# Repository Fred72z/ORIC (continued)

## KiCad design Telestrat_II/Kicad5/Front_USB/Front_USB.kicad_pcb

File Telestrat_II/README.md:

# TELESTRAT II

Le TELESTRAT II est un TELESTRAT au format mini-ITX qui prend place dans un boîtier HTPC.
En plus des caractéristiques du TELESTRAT, la machine dispose en interne d'une horloge RTC, de 512Ko de ROM et de 144Ko de RAM et d'un lecteur GOTEK.
La machine est un mix entre l'ORIC ATMOS et le TELESTRAT. Elle dispose de 8 modes de fonctionnement allant de l'ORIC1 au TELESTRAT.
Elle est parfaitement compatible avec ses prédécesseurs ORIC1/ATMOS et microdisc.

Mode ORIC1

Mode ORIC ATMOS avec SEDORIC

Mode TELESTRAT HYPERBASIC

Intérieur de la boîte

Platine principale seule

# Connecteurs

Les connecteurs sont tous disposés à l'arrière de la machine à l'exception du port d'extension placé sur la carte mère.

**AUDIO/VIDEO**

- 1 : REMOTE 
- 2 : +5V
- 3 : REMOTE 
- 4 : K7 IN
- 5 : K7 OUT
- 6 : NC
- 7 : SYNC
- 8 : ROUGE
- 9 : SOUND OUT
- 10 : GND
- 11 : VERT
- 12 : BLEU
- 13 : GND
- SHIELD : GND

**MINITEL/MIDI**

- 1  : GND
- 2  : BAUD_RATE
- 3  : PA3
- 4  : MINITEL_DATA_OUT
- 5  : PA6
- 6  : MINITEL_DATA_IN
- 7  : CB2
- 8  : CARRIER
- 9  : NC
- 10 : NC
- 11 : CA1
- 12 : CB1
- 13 : +5V
- 14 : GND

**IMPRIMANTE**

- 1  : /STB
- 3  : D0
- 5  : D1
 -7  : D2
 -9  : D3
- 11 : D4
- 13 : D5
- 15 : D6
- 17 : D7
- 19 : /ACK
- 2,4,...,20 : GND

**CLAVIER**

- 1  : COL0
- 2  : COL1
- 3  : COL2
- 4  : COL3
- 5  : COL7
- 6  : KBD2
- 7  : KBD1
- 8  : KBD0
- 9  : COL6
- 10 : COL5
- 11 : COL4
- 12 : KB
- 13 : +5V
- SHIELD : GND

**JOYSTICK GAUCHE**

- 1 : HAUT
- 2 : BAS
- 3 : GAUCHE
- 4 : DROIT
- 5 : NC
- 6 : TIR
- 7 : +5V
- 8 : GND
- 9 : NC

**JOYSTICK DROIT**

- 1 : HAUT
- 2 : BAS
- 3 : GAUCHE
- 4 : DROIT
- 5 : TIR2
- 6 : TIR
- 7 : +5V
- 8 : GND
- 9 : TIR3

**EXPANSION**
Un port d'extension est placé sur la carte principale. Il permet d'ajouter des périphériques en page 3 uniquement. Son brochage est le suivant:
[à venir]

# Modes de fonctionnement

Le Telestrat II dispose de 8 modes différents permettant de reproduire le fonctionnement de l'ORIC1, l'oric ATMOS ou l'oric TELESTRAT. Ces modes sont sélectionnés grace à 3 micro-interrupteurs "piano" accessibles à l'arrière de la machine.

4 modes sont réservés aux ORIC1/ATMOS et 4 modes sont réservés au TELESTRAT.

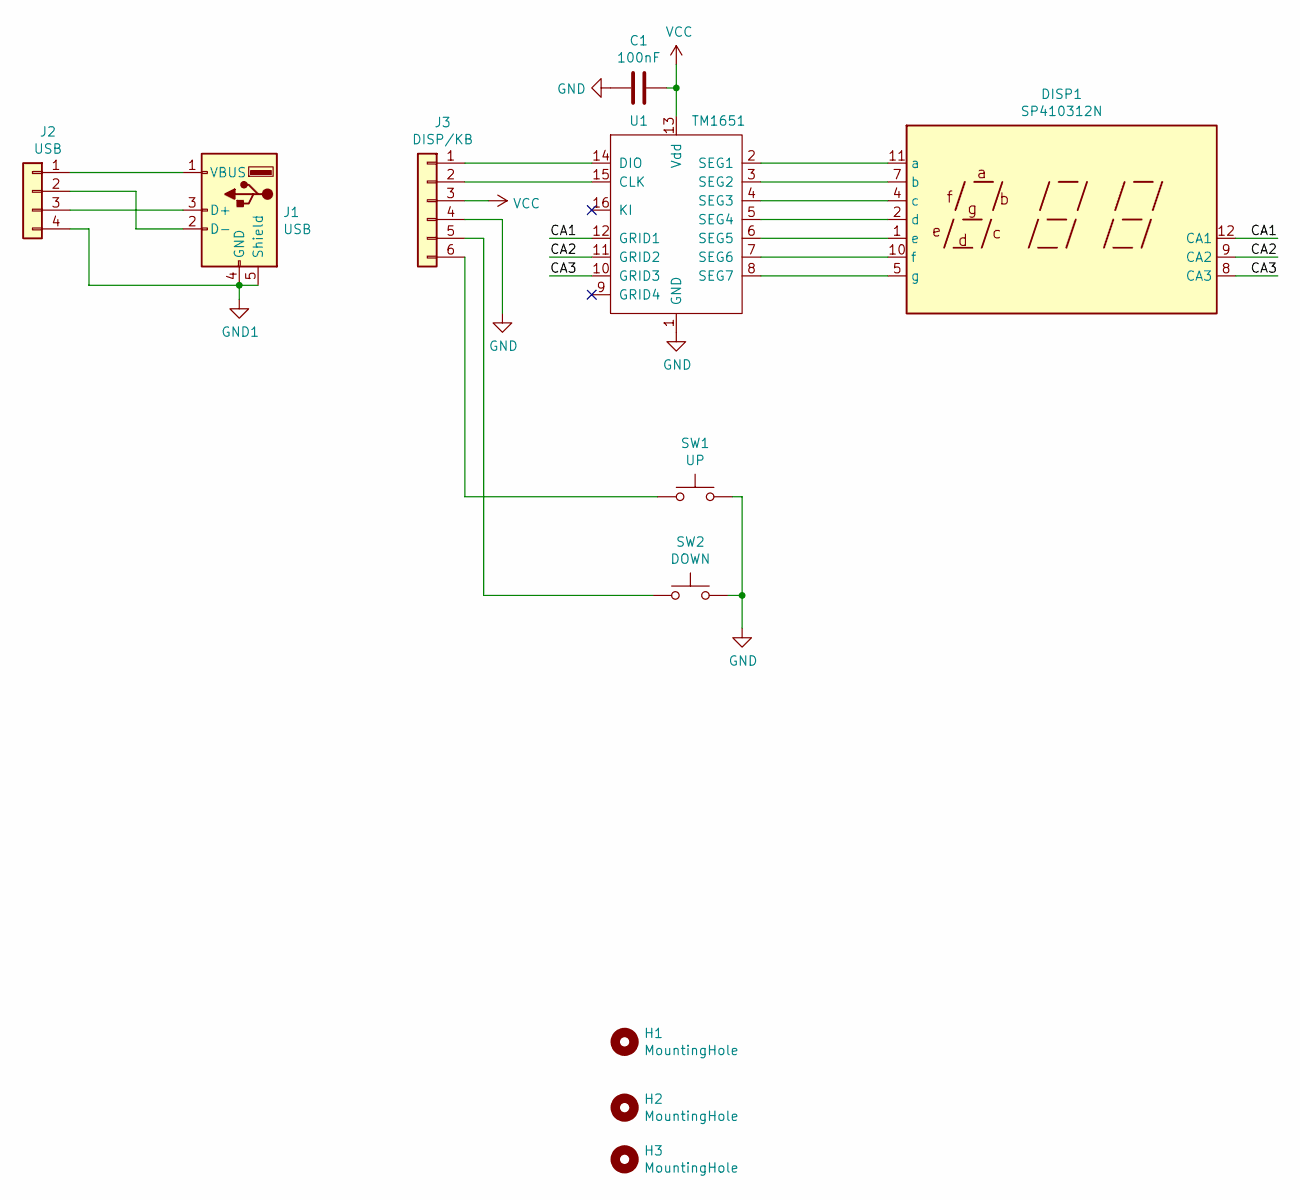
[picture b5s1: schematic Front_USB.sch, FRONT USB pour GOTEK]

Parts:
C1: 100nF; C_0805_2012Metric
DISP1: SP410312N; SP410312SPN
H1, H2: MountingHole; MountingHole_4.3mm_M4
H3: MountingHole; MountingHole_2.2mm_M2
J1: USB; USB_A_Vertical
J2: USB; PinHeader_1x04_P2.54mm_Vertical
J3: DISP/KB; PinHeader_1x06_P2.54mm_Vertical
SW1: UP; SW_PUSH_6mm
SW2: DOWN; SW_PUSH_6mm
U1: TM1651; SO-16_3.9x9.9mm_P1.27mm

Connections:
/CA1: DISP1.12 (CA1), U1.12 (GRID1)
/CA2: DISP1.9 (CA2), U1.11 (GRID2)
/CA3: DISP1.8 (CA3), U1.10 (GRID3)
GND: C1.2, J3.4, SW1.2, SW2.2, U1.1 (GND)
GND1: J1.4 (GND), J1.5 (Shield), J2.4
unnamed: DISP1.1 (e), U1.6 (SEG5)
unnamed: DISP1.2 (d), U1.5 (SEG4)
unnamed: DISP1.4 (c), U1.4 (SEG3)
unnamed: DISP1.5 (g), U1.8 (SEG7)
unnamed: DISP1.7 (b), U1.3 (SEG2)
unnamed: DISP1.10 (f), U1.7 (SEG6)
unnamed: DISP1.11 (a), U1.2 (SEG1)
unnamed: J1.1 (VBUS), J2.1
unnamed: J1.2 (D-), J2.2
unnamed: J1.3 (D+), J2.3
unnamed: J3.1, U1.14 (DIO)
unnamed: J3.2, U1.15 (CLK)
unnamed: J3.5, SW2.1
unnamed: J3.6, SW1.1
VCC: C1.1, J3.3, U1.13 (Vdd)

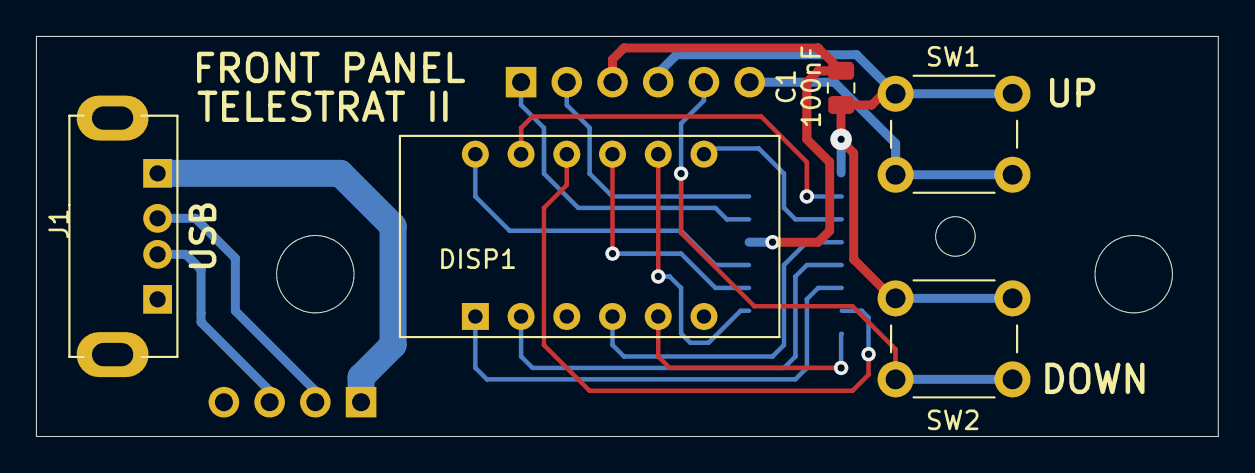
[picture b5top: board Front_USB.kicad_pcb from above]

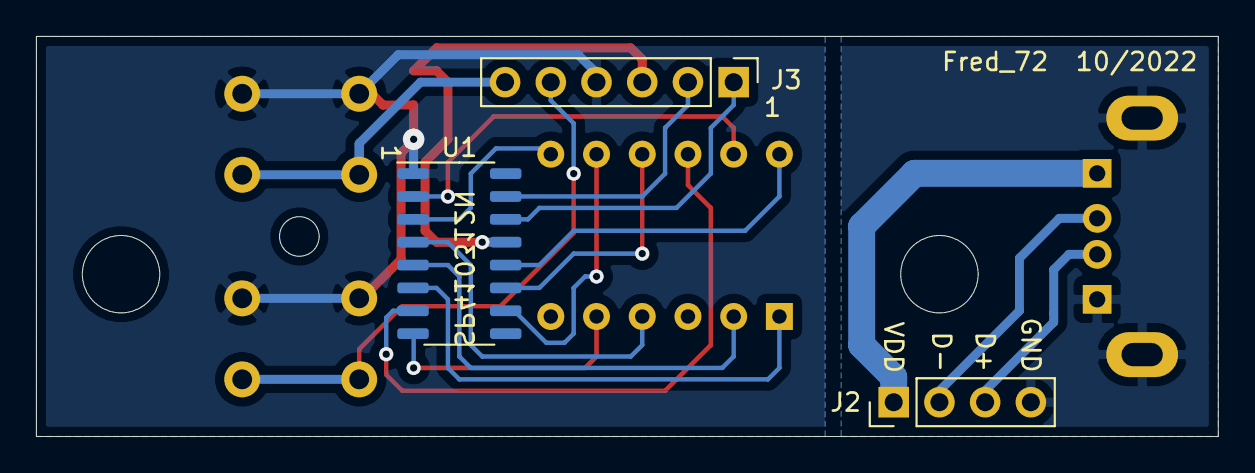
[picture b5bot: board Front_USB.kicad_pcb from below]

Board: 2 copper layers, 65.7 x 22.2 mm, 11 parts (3 on the bottom side), 20 nets.

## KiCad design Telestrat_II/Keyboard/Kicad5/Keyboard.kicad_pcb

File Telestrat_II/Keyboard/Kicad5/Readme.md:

# CLAVIER TELESTRAT II

Les touches du clavier sont des CHERRY ou GATERON (rouge).
La barre d'espace reçoit 2 touches (préférable) ou une seule touche (ajout d'une barre pour l'équilibrer).
La vue 3D du PCB montre 3 touches pour la barre d'espace mais il ne faut en mettre qu'une ou deux.

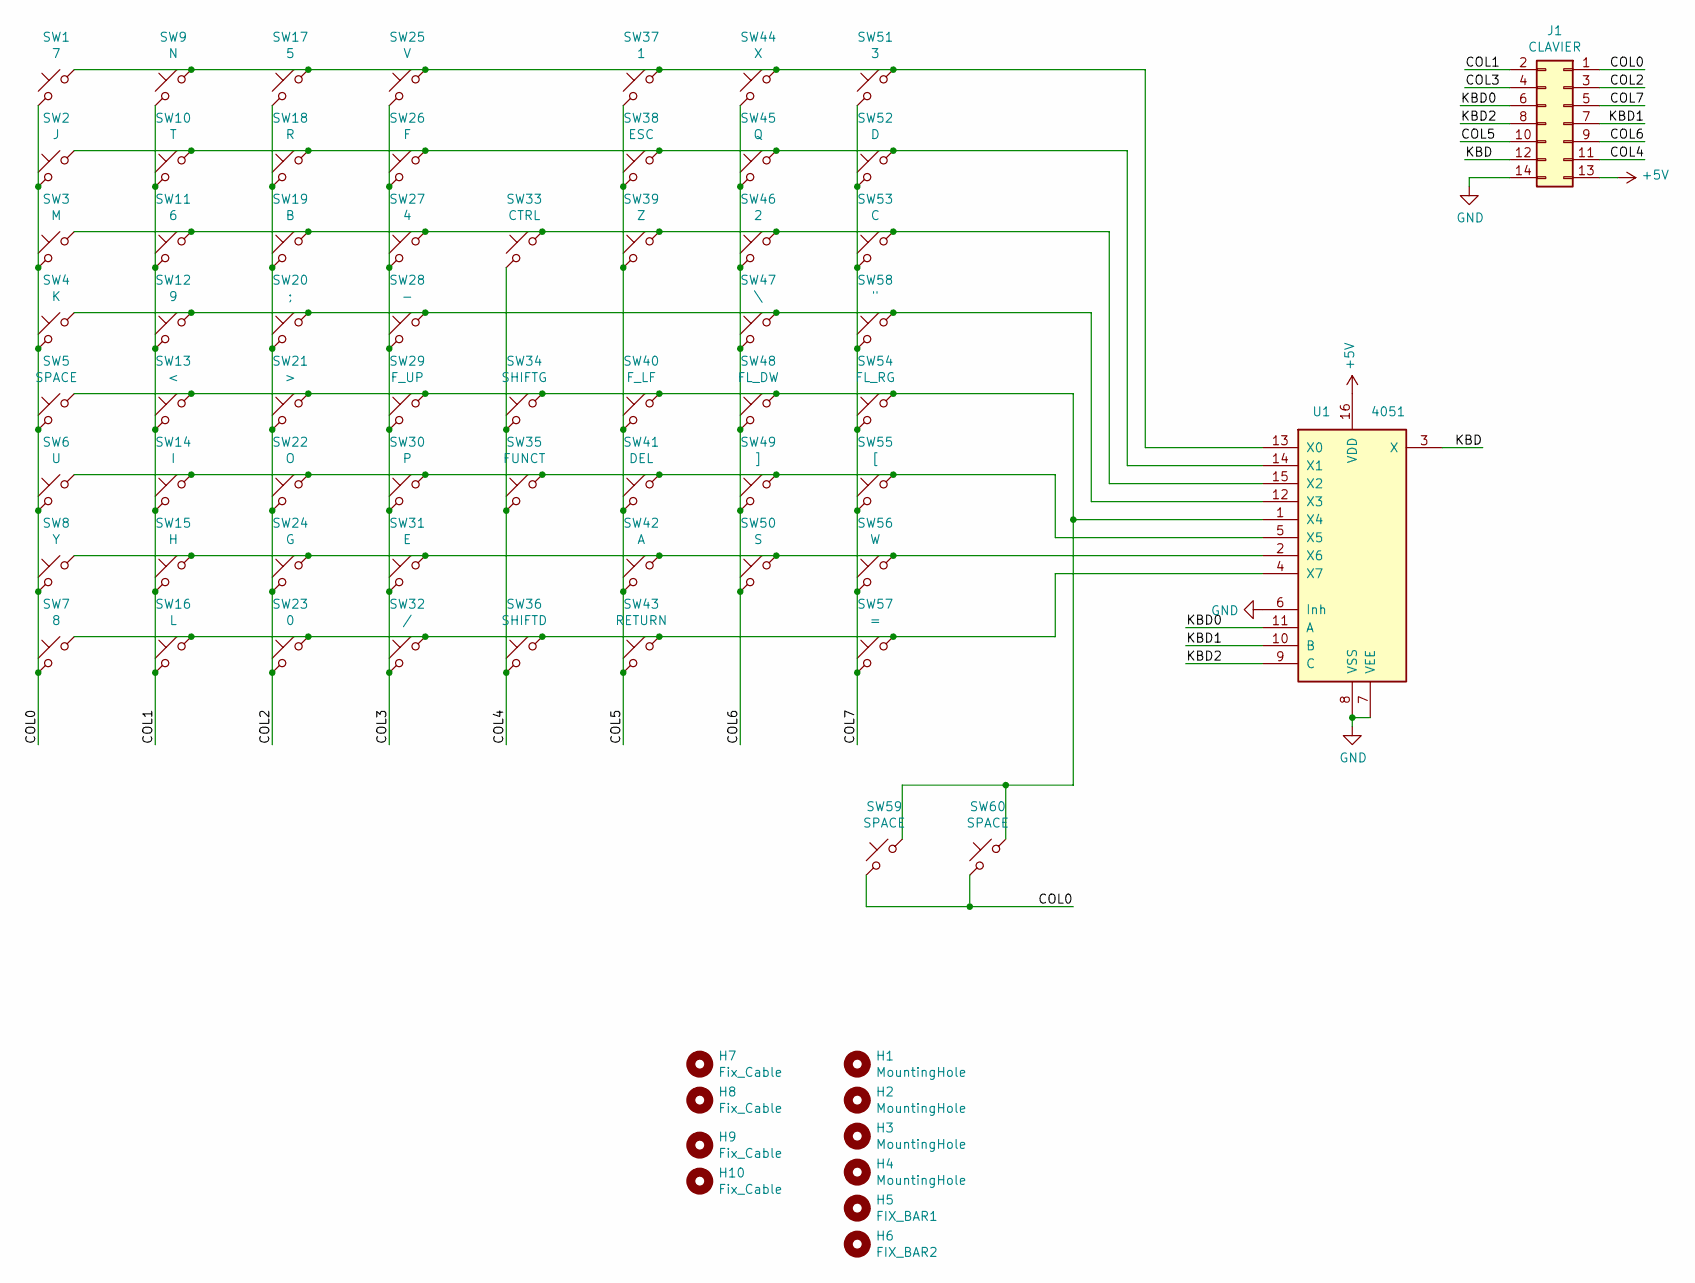
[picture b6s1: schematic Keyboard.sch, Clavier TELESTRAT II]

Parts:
H1, H2, H3, H4: MountingHole; MountingHole_3.2mm_M3_DIN965_Pad
H5: FIX_BAR1; MountingHole_3.2mm_M3_DIN965_Pad
H6: FIX_BAR2; MountingHole_3.2mm_M3_DIN965_Pad
H7, H8, H9, H10: Fix_Cable; MountingHole_2.2mm_M2_DIN965_Pad
J1: CLAVIER; PinHeader_2x07_P2.54mm_Vertical
SW1: 7; SW_Gateron_MX_1.00u_Plate
SW2: J; SW_Gateron_MX_1.00u_Plate
SW3: M; SW_Gateron_MX_1.00u_Plate
SW4: K; SW_Gateron_MX_1.00u_Plate
SW5: SPACE; SW_Gateron_MX_6.25u_Plate
SW6: U; SW_Gateron_MX_1.00u_Plate
SW7: 8; SW_Gateron_MX_1.00u_Plate
SW8: Y; SW_Gateron_MX_1.00u_Plate
SW9: N; SW_Gateron_MX_1.00u_Plate
SW10: T; SW_Gateron_MX_1.00u_Plate
SW11: 6; SW_Gateron_MX_1.00u_Plate
SW12: 9; SW_Gateron_MX_1.00u_Plate
SW13: <; SW_Gateron_MX_1.00u_Plate
SW14: I; SW_Gateron_MX_1.00u_Plate
SW15: H; SW_Gateron_MX_1.00u_Plate
SW16: L; SW_Gateron_MX_1.00u_Plate
SW17: 5; SW_Gateron_MX_1.00u_Plate
SW18: R; SW_Gateron_MX_1.00u_Plate
SW19: B; SW_Gateron_MX_1.00u_Plate
SW20: ;; SW_Gateron_MX_1.00u_Plate
SW21: >; SW_Gateron_MX_1.00u_Plate
SW22: O; SW_Gateron_MX_1.00u_Plate
SW23: 0; SW_Gateron_MX_1.00u_Plate
SW24: G; SW_Gateron_MX_1.00u_Plate
SW25: V; SW_Gateron_MX_1.00u_Plate
SW26: F; SW_Gateron_MX_1.00u_Plate
SW27: 4; SW_Gateron_MX_1.00u_Plate
SW28: -; SW_Gateron_MX_1.00u_Plate
SW29: F_UP; SW_Gateron_MX_1.00u_Plate
SW30: P; SW_Gateron_MX_1.00u_Plate
SW31: E; SW_Gateron_MX_1.00u_Plate
SW32: /; SW_Gateron_MX_1.00u_Plate
SW33: CTRL; SW_Gateron_MX_1.25u_Plate
SW34: SHIFTG; SW_Gateron_MX_1.25u_Plate
SW35: FUNCT; SW_Gateron_MX_1.25u_Plate
SW36: SHIFTD; SW_Gateron_MX_2.25u_Plate
SW37: 1; SW_Gateron_MX_1.00u_Plate
SW38: ESC; SW_Gateron_MX_1.00u_Plate
SW39: Z; SW_Gateron_MX_1.00u_Plate
SW40: F_LF; SW_Gateron_MX_1.00u_Plate
SW41: DEL; SW_Gateron_MX_2.00u_Plate
SW42: A; SW_Gateron_MX_1.00u_Plate
SW43: RETURN; SW_Gateron_MX_2.25u_Plate
SW44: X; SW_Gateron_MX_1.00u_Plate
SW45: Q; SW_Gateron_MX_1.00u_Plate
SW46: 2; SW_Gateron_MX_1.00u_Plate
SW47: \\; SW_Gateron_MX_1.50u_Plate
SW48: FL_DW; SW_Gateron_MX_1.00u_Plate
SW49: ]; SW_Gateron_MX_1.00u_Plate
SW50: S; SW_Gateron_MX_1.00u_Plate
SW51: 3; SW_Gateron_MX_1.00u_Plate
SW52: D; SW_Gateron_MX_1.00u_Plate
SW53: C; SW_Gateron_MX_1.00u_Plate
SW54: FL_RG; SW_Gateron_MX_1.00u_Plate
SW55: [; SW_Gateron_MX_1.00u_Plate
SW56: W; SW_Gateron_MX_1.00u_Plate
SW57: =; SW_Gateron_MX_1.00u_Plate
SW58: \"; SW_Gateron_MX_1.00u_Plate
SW59, SW60: SPACE; SW_Gateron_MX_1.00u_Plate
U1: 4051; DIP-16_W7.62mm

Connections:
+5V: J1.13, U1.16 (VDD)
/COL0: J1.1, SW1.2, SW2.2, SW3.2, SW4.2, SW5.2, SW6.2, SW7.2, SW8.2, SW59.2, SW60.2
/COL1: J1.2, SW9.2, SW10.2, SW11.2, SW12.2, SW13.2, SW14.2, SW15.2, SW16.2
/COL2: J1.3, SW17.2, SW18.2, SW19.2, SW20.2, SW21.2, SW22.2, SW23.2, SW24.2
/COL3: J1.4, SW25.2, SW26.2, SW27.2, SW28.2, SW29.2, SW30.2, SW31.2, SW32.2
/COL4: J1.11, SW33.2, SW34.2, SW35.2, SW36.2
/COL5: J1.10, SW37.2, SW38.2, SW39.2, SW40.2, SW41.2, SW42.2, SW43.2
/COL6: J1.9, SW44.2, SW45.2, SW46.2, SW47.2, SW48.2, SW49.2, SW50.2
/COL7: J1.5, SW51.2, SW52.2, SW53.2, SW54.2, SW55.2, SW56.2, SW57.2, SW58.2
/KBD: J1.12, U1.3 (X)
/KBD0: J1.6, U1.11 (A)
/KBD1: J1.7, U1.10 (B)
/KBD2: J1.8, U1.9 (C)
GND: J1.14, U1.6 (Inh), U1.7 (VEE), U1.8 (VSS)
unnamed: SW1.1, SW9.1, SW17.1, SW25.1, SW37.1, SW44.1, SW51.1, U1.13 (X0)
unnamed: SW2.1, SW10.1, SW18.1, SW26.1, SW38.1, SW45.1, SW52.1, U1.14 (X1)
unnamed: SW3.1, SW11.1, SW19.1, SW27.1, SW33.1, SW39.1, SW46.1, SW53.1, U1.15 (X2)
unnamed: SW4.1, SW12.1, SW20.1, SW28.1, SW47.1, SW58.1, U1.12 (X3)
unnamed: SW5.1, SW13.1, SW21.1, SW29.1, SW34.1, SW40.1, SW48.1, SW54.1, SW59.1, SW60.1, U1.1 (X4)
unnamed: SW6.1, SW14.1, SW22.1, SW30.1, SW35.1, SW41.1, SW49.1, SW55.1, U1.5 (X5)
unnamed: SW8.1, SW15.1, SW24.1, SW31.1, SW42.1, SW50.1, SW56.1, U1.2 (X6)
unnamed: SW7.1, SW16.1, SW23.1, SW32.1, SW36.1, SW43.1, SW57.1, U1.4 (X7)

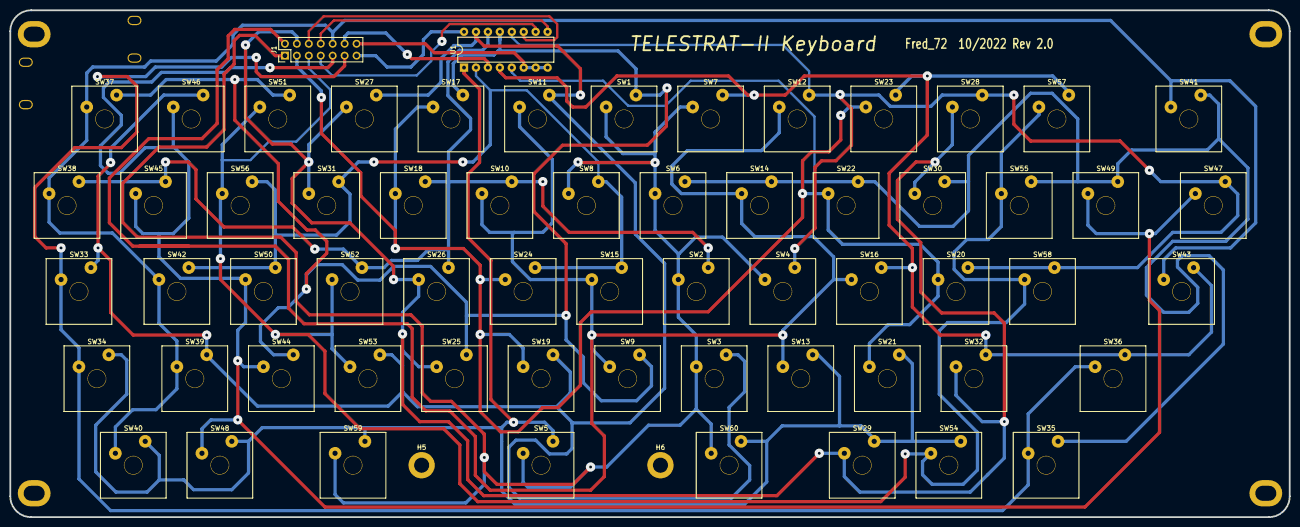
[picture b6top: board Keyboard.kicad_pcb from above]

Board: 2 copper layers, 272.2 x 107.8 mm, 72 parts (0 on the bottom side), 22 nets.

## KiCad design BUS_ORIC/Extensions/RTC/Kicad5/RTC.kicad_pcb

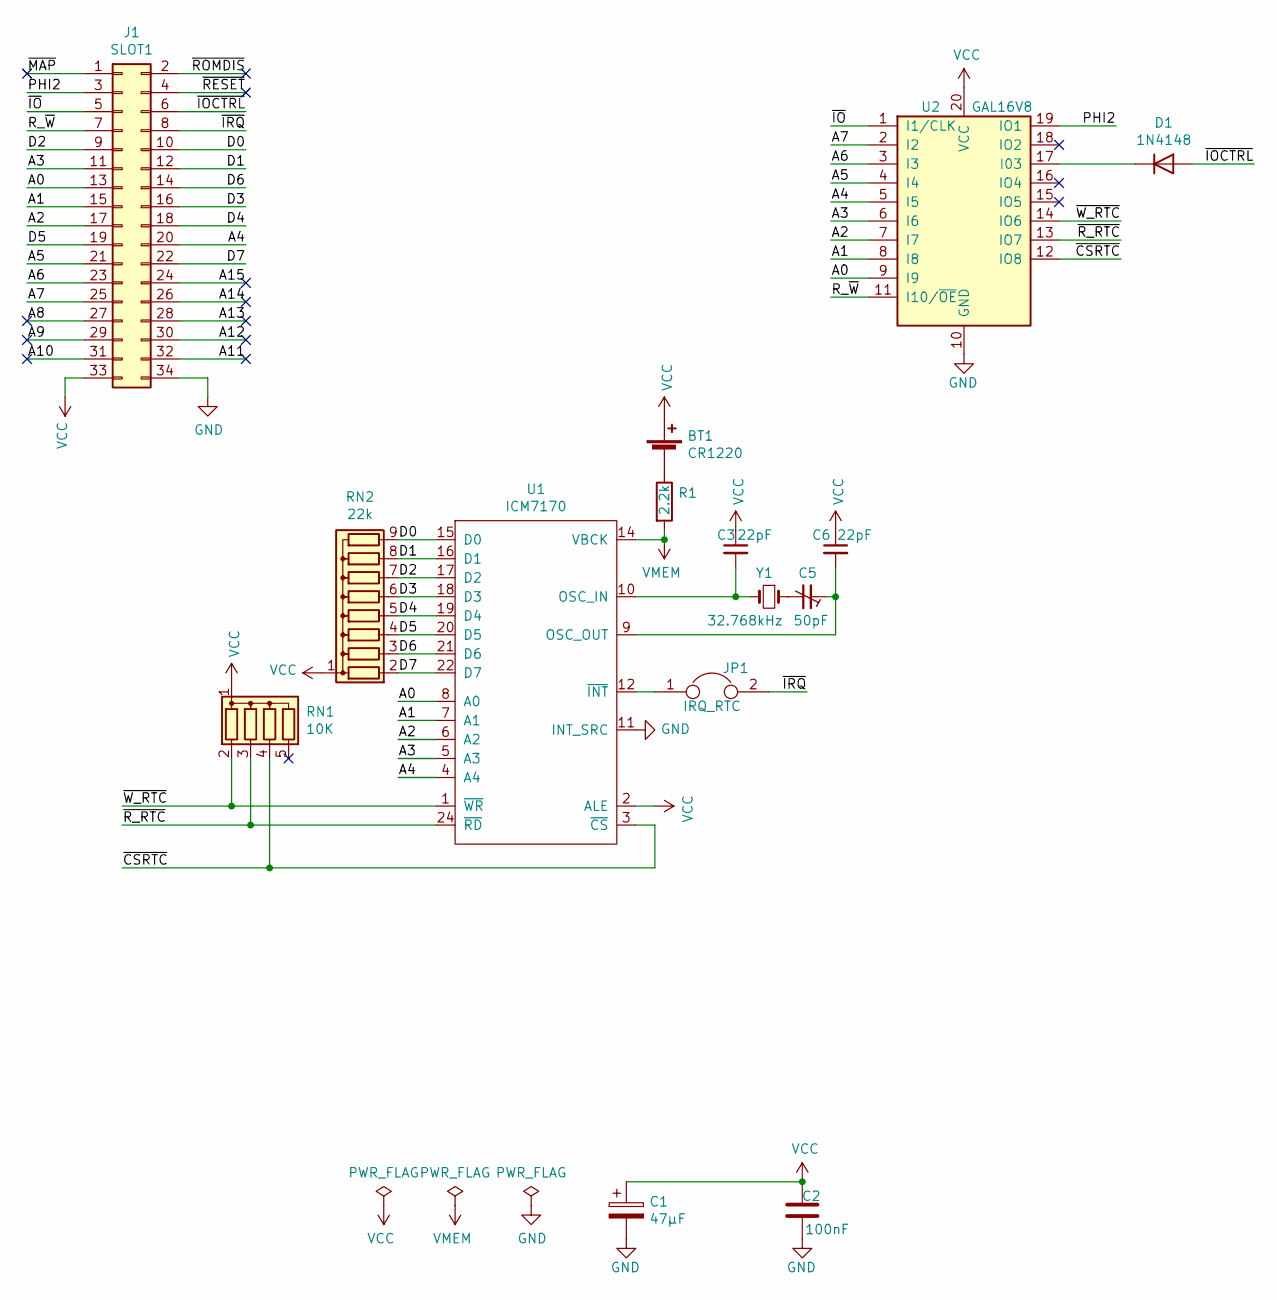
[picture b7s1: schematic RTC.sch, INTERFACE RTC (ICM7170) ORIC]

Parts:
BT1: CR1220; BatteryHolder_BC501SM
C1: 47µF; CP_Radial_D5.0mm_P2.00mm
C2: 100nF; C_Rect_L7.0mm_W2.5mm_P5.00mm
C3, C6: 22pF; C_Disc_D4.3mm_W1.9mm_P5.00mm
C5: 50pF; Trimmer_Cap_TZ03F
D1: 1N4148; D_DO-35_SOD27_P7.62mm_Horizontal
J1: SLOT1; IDC-Header_2x17_P2.54mm_Horizontal
JP1: IRQ_RTC; PinHeader_1x02_P2.54mm_Vertical
R1: 2.2k; R_Axial_DIN0204_L3.6mm_D1.6mm_P7.62mm_Horizontal
RN1: 10K; R_Array_SIP5
RN2: 22k; R_Array_SIP9
U1: ICM7170; DIP-24_W15.24mm_LongPads
U2: GAL16V8; DIP-20_W7.62mm_LongPads
Y1: 32.768kHz; Crystal_AT310_D3.0mm_L10.0mm_Horizontal_1EP_style2

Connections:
/A0: J1.13, U1.8 (A0), U2.9 (I9)
/A1: J1.15, U1.7 (A1), U2.8 (I8)
/A2: J1.17, U1.6 (A2), U2.7 (I7)
/A3: J1.11, U1.5 (A3), U2.6 (I6)
/A4: J1.20, U1.4 (A4), U2.5 (I5)
/A5: J1.21, U2.4 (I4)
/A6: J1.23, U2.3 (I3)
/A7: J1.25, U2.2 (I2)
/A8: J1.27
/A9: J1.29
/A10: J1.31
/A11: J1.32
/A12: J1.30
/A13: J1.28
/A14: J1.26
/A15: J1.24
/D0: J1.10, RN2.9 (R8), U1.15 (D0)
/D1: J1.12, RN2.8 (R7), U1.16 (D1)
/D2: J1.9, RN2.7 (R6), U1.17 (D2)
/D3: J1.16, RN2.6 (R5), U1.18 (D3)
/D4: J1.18, RN2.5 (R4), U1.19 (D4)
/D5: J1.19, RN2.4 (R3), U1.20 (D5)
/D6: J1.14, RN2.3 (R2), U1.21 (D6)
/D7: J1.22, RN2.2 (R1), U1.22 (D7)
/PHI2: J1.3, U2.19 (IO1)
/R_~W: J1.7, U2.11 (I10/~OE~)
/~CSRTC: RN1.4 (R3), U1.3 (~CS), U2.12 (IO8)
/~IO: J1.5, U2.1 (I1/CLK)
/~IOCTRL: D1.2 (A), J1.6
/~IRQ: J1.8, JP1.2
/~MAP: J1.1
/~RESET: J1.4
/~ROMDIS: J1.2
/~R_RTC: RN1.3 (R2), U1.24 (~RD), U2.13 (IO7)
/~W_RTC: RN1.2 (R1), U1.1 (~WR), U2.14 (IO6)
GND: C1.2, C2.1, J1.34, U1.11 (INT_SRC), U1.13 (GND), U2.10 (GND)
unnamed: BT1.2 (-), R1.1
unnamed: C3.2, U1.10 (OSC_IN), Y1.2
unnamed: C5.1, C6.2, U1.9 (OSC_OUT)
unnamed: C5.2, Y1.1
unnamed: D1.1 (K), U2.17 (I03)
unnamed: JP1.1, U1.12 (~INT)
VCC: BT1.1 (+), C1.1, C2.2, C3.1, C6.1, J1.33, RN1.1 (common), RN2.1 (common), U1.2 (ALE), U1.23 (VCC), U2.20 (VCC)
VMEM: R1.2, U1.14 (VBCK)

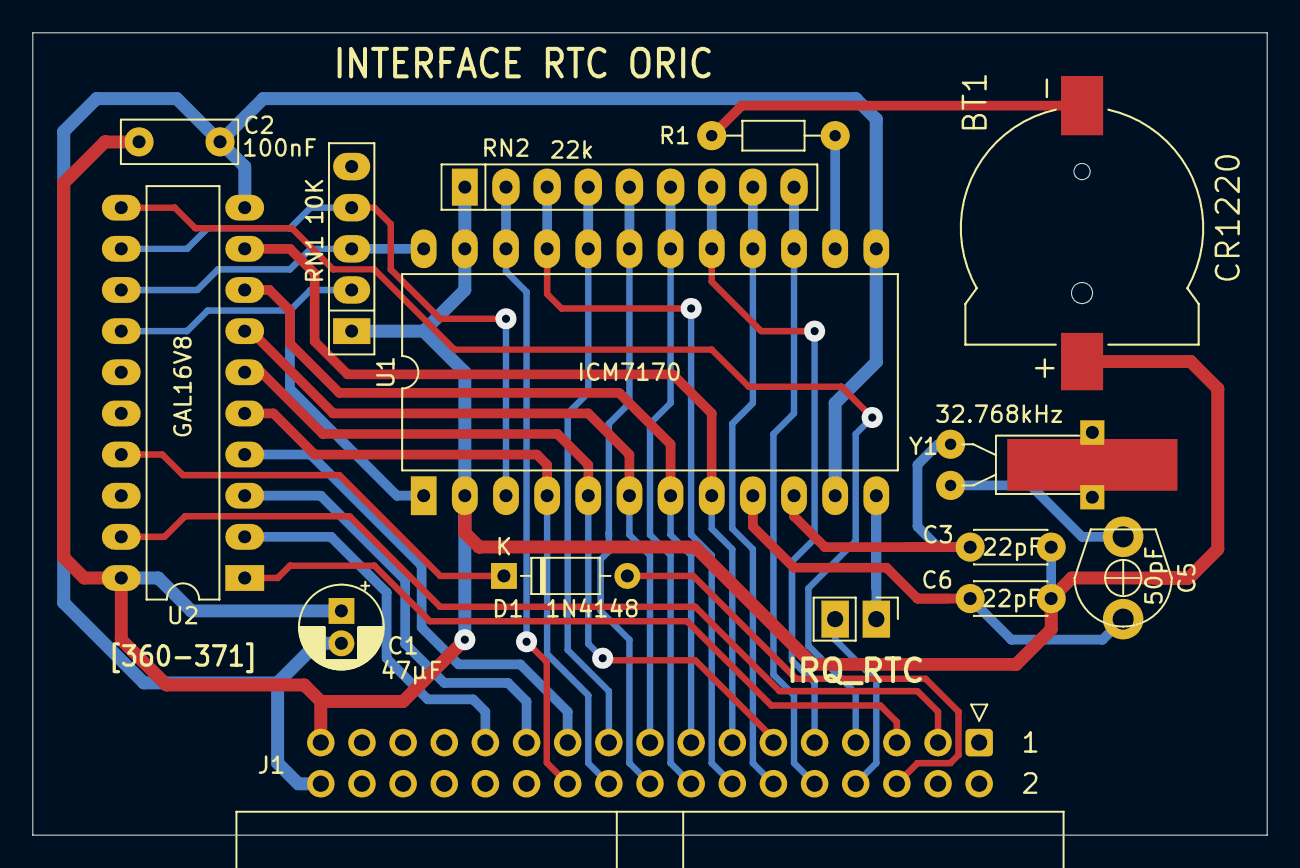
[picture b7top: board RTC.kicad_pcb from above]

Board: 2 copper layers, 76.2 x 49.5 mm, 15 parts (0 on the bottom side), 33 nets.

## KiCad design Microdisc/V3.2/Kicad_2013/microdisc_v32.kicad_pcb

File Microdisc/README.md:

# Microdisc
Nouveau contrôleur compatible microdisc

Ce contrôleur reprend le schéma du contrôleur microdisc original mais remplace les portes logiques par un circuit CPLD afin de réduire sa taille.
Il se loge ainsi sous un lecteur de disquettes 3.5" classique pour la version 3.2 et sous un lecteur gotek pour la version 3.4 (un peu plus court).
Ils sont presque identiques sauf au niveau des buffers 74HCT541 pour la version 3.2 et 74HCT244 pour la version 3.4.

__Version 3.2 (lecteur 3.5")__

__Version 3.4 (lecteur Gotek)__

Le fonctionnement reste identique au microdisc d'origine.

La ROM est identique pour les 2 versions. Le PCB accepte des 27C64/128/256 ou 512.
Mais le fonctionnement est très sensible aux composants utilisés (classique avec l'Oric), notamment l'EPROM et les Buffers.
J'obtiens un bon fonctionnement avec des EPROM 27C512 "petite puce" et des circuits HCT.

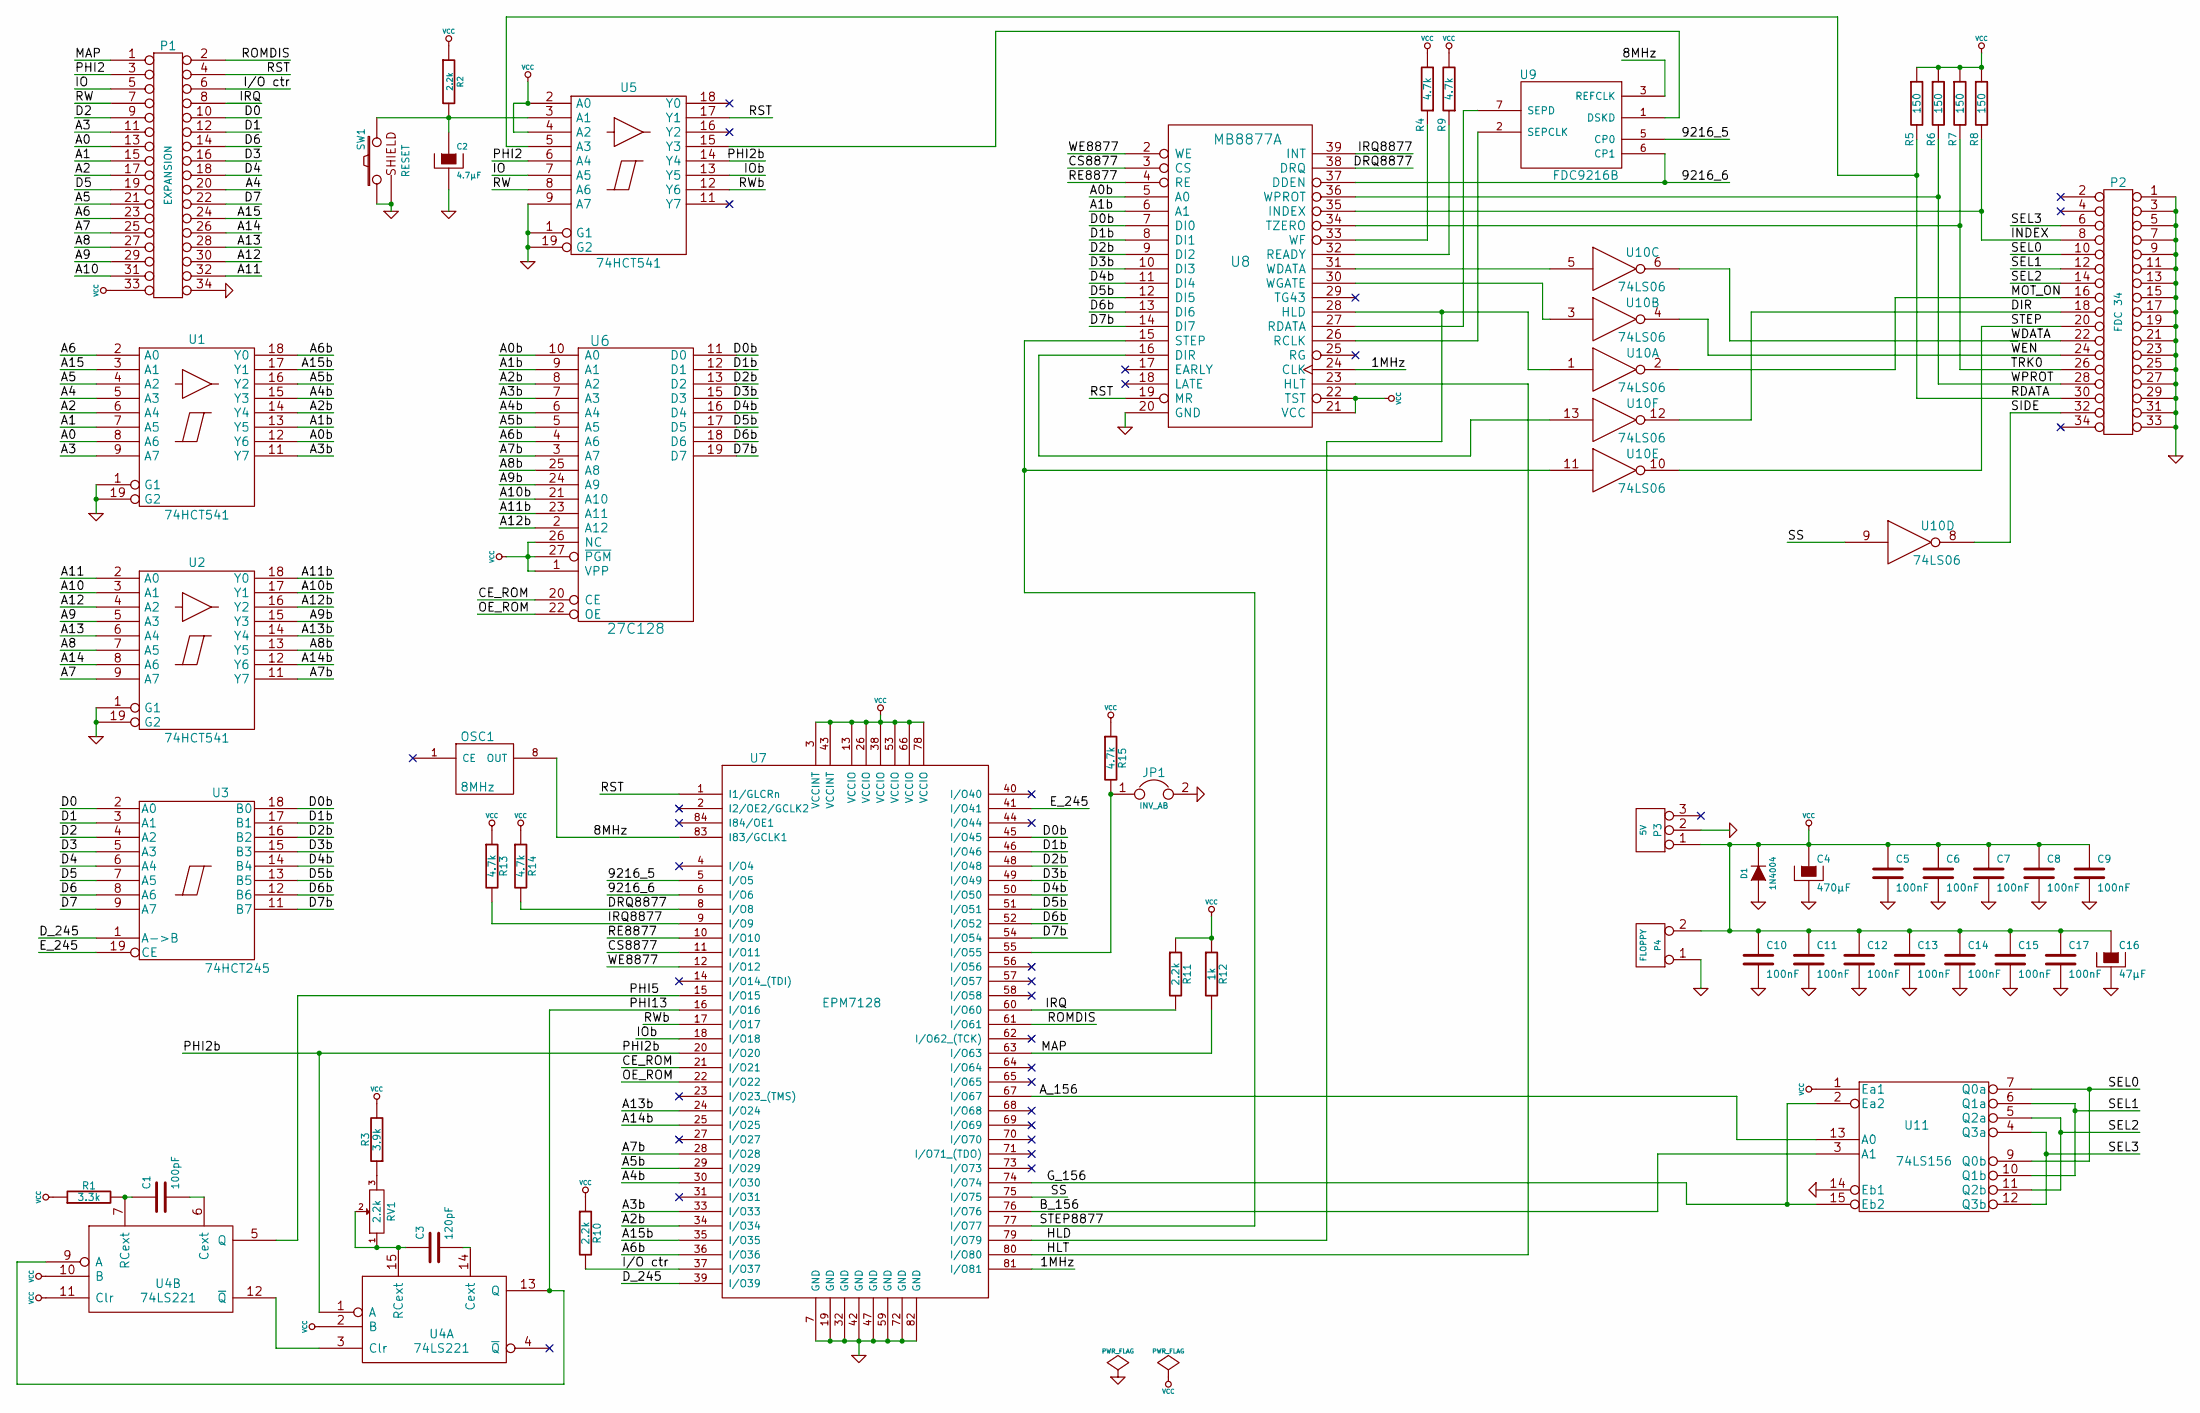
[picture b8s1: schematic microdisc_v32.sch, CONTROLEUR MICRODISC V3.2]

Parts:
C1: 100pF
C2: 4.7µF
C3: 120pF
C4: 470µF
C5, C6, C7, C8, C9, C10, C11, C12, C13, C14, C15, C17: 100nF
C16: 47µF
D1: 1N4004
JP1: INV_AB
OSC1: 8MHz
P1: EXPANSION
P2: FDC 34
P3: 5V
P4: FLOPPY
R1: 3.3k
R2, R10, R11: 2.2k
R3: 3.9k
R4, R9, R13, R14, R15: 4.7k
R5, R6, R7, R8: 150
R12: 1k
RV1: 2.2k
SW1: RESET
U1, U2, U5: 74HCT541
U3: 74HCT245
U4: 74LS221
U6: 27C128
U7: EPM7128
U8: MB8877A
U9: FDC9216B
U10: 74LS06
U11: 74LS156

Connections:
/1MHz: U7.81 (I/O81), U8.24 (CLK)
/8MHz: OSC1.8 (OUT), U7.83 (I83/GCLK1), U9.3 (REFCLK)
/9216_5: U7.5 (I/O5), U9.5 (CP0)
/9216_6: U7.6 (I/O6), U8.37 (DDEN), U9.6 (CP1)
/A0: P1.13, U1.8 (A6)
/A0b: U1.12 (Y6), U6.10 (A0), U8.5 (A0)
/A1: P1.15, U1.7 (A5)
/A1b: U1.13 (Y5), U6.9 (A1), U8.6 (A1)
/A2: P1.17, U1.6 (A4)
/A2b: U1.14 (Y4), U6.8 (A2), U7.34 (I/O34)
/A3: P1.11, U1.9 (A7)
/A3b: U1.11 (Y7), U6.7 (A3), U7.33 (I/O33)
/A4: P1.20, U1.5 (A3)
/A4b: U1.15 (Y3), U6.6 (A4), U7.30 (I/O30)
/A5: P1.21, U1.4 (A2)
/A5b: U1.16 (Y2), U6.5 (A5), U7.29 (I/O29)
/A6: P1.23, U1.2 (A0)
/A6b: U1.18 (Y0), U6.4 (A6), U7.36 (I/O36)
/A7: P1.25, U2.9 (A7)
/A7b: U2.11 (Y7), U6.3 (A7), U7.28 (I/O28)
/A8: P1.27, U2.7 (A5)
/A8b: U2.13 (Y5), U6.25 (A8)
/A9: P1.29, U2.5 (A3)
/A9b: U2.15 (Y3), U6.24 (A9)
/A10: P1.31, U2.3 (A1)
/A10b: U2.17 (Y1), U6.21 (A10)
/A11: P1.32, U2.2 (A0)
/A11b: U2.18 (Y0), U6.23 (A11)
/A12: P1.30, U2.4 (A2)
/A12b: U2.16 (Y2), U6.2 (A12)
/A13: P1.28, U2.6 (A4)
/A13b: U2.14 (Y4), U7.24 (I/O24)
/A14: P1.26, U2.8 (A6)
/A14b: U2.12 (Y6), U7.25 (I/O25)
/A15: P1.24, U1.3 (A1)
/A15b: U1.17 (Y1), U7.35 (I/O35)
/A_156: U7.67 (I/O67), U11.13 (A0)
/B_156: U7.76 (I/O76), U11.3 (A1)
/CE_ROM: U6.20 (CE), U7.21 (I/O21)
/CS8877: U7.11 (I/O11), U8.3 (CS)
/D0: P1.10, U3.2 (A0)
/D0b: U3.18 (B0), U6.11 (D0), U7.45 (I/O45), U8.7 (DI0)
/D1: P1.12, U3.3 (A1)
/D1b: U3.17 (B1), U6.12 (D1), U7.46 (I/O46), U8.8 (DI1)
/D2: P1.9, U3.4 (A2)
/D2b: U3.16 (B2), U6.13 (D2), U7.48 (I/O48), U8.9 (DI2)
/D3: P1.16, U3.5 (A3)
/D3b: U3.15 (B3), U6.15 (D3), U7.49 (I/O49), U8.10 (DI3)
/D4: P1.18, U3.6 (A4)
/D4b: U3.14 (B4), U6.16 (D4), U7.50 (I/O50), U8.11 (DI4)
/D5: P1.19, U3.7 (A5)
/D5b: U3.13 (B5), U6.17 (D5), U7.51 (I/O51), U8.12 (DI5)
/D6: P1.14, U3.8 (A6)
/D6b: U3.12 (B6), U6.18 (D6), U7.52 (I/O52), U8.13 (DI6)
/D7: P1.22, U3.9 (A7)
/D7b: U3.11 (B7), U6.19 (D7), U7.54 (I/O54), U8.14 (DI7)
/DIR: P2.18, U10.12
/DRQ8877: R14.2, U7.8 (I/O8), U8.38 (DRQ)
/D_245: U3.1 (A->B), U7.39 (I/O39)
/E_245: U3.19 (CE), U7.41 (I/O41)
/G_156: U7.74 (I/O74), U11.2 (Ea2), U11.15 (Eb2)
/HLD: U7.79 (I/O79), U8.28 (HLD), U10.1
/HLT: U7.80 (I/O80), U8.23 (HLT)
/I/O ctr: P1.6, R10.2, U7.37 (I/O37)
/INDEX: P2.8, R8.2, U8.35 (INDEX)
/IO: P1.5, U5.7 (A5)
/IOb: U5.13 (Y5), U7.18 (I/O18)
/IRQ: P1.8, R11.2, U7.60 (I/O60)
/IRQ8877: R13.2, U7.9 (I/O9), U8.39 (INT)
/MAP: P1.1, R12.2, U7.63 (I/O63)
/MOT_ON: P2.16, U10.2
/OE_ROM: U6.22 (OE), U7.22 (I/O22)
/PHI2: P1.3, U5.6 (A4)
/PHI2b: U4.1 (A), U5.14 (Y4), U7.20 (I/O20)
/PHI5: U4.5 (Q), U7.15 (I/O15)
/PHI13: U4.9 (A), U4.13 (Q), U7.16 (I/O16)
/RDATA: P2.30, R5.2, U5.5 (A3)
/RE8877: U7.10 (I/O10), U8.4 (RE)
/ROMDIS: P1.2, U7.61 (I/O61)
/RST: P1.4, U5.17 (Y1), U7.1 (I1/GLCRn), U8.19 (MR)
/RW: P1.7, U5.8 (A6)
/RWb: U5.12 (Y6), U7.17 (I/O17)
/SEL0: P2.10, U11.7 (Q0a), U11.9 (Q0b)
/SEL1: P2.12, U11.6 (Q1a), U11.10 (Q1b)
/SEL2: P2.14, U11.5 (Q2a), U11.11 (Q2b)
/SEL3: P2.6, U11.4 (Q3a), U11.12 (Q3b)
/SIDE: P2.32, U10.8
/SS: U7.75 (I/O75), U10.9
/STEP: P2.20, U10.10
/STEP8877: U7.77 (I/O77), U8.15 (STEP), U10.11
/TRK0: P2.26, R7.2, U8.34 (TZERO)
/WDATA: P2.22, U10.6
/WE8877: U7.12 (I/O12), U8.2 (WE)
/WEN: P2.24, U10.4
/WPROT: P2.28, R6.2, U8.36 (WPROT)
GND: C2.2, C4.2, C5.2, C6.2, C7.2, C8.2, C9.2, C10.2, C11.2, C12.2, C13.2, C14.2, C15.2, C16.2, C17.2, D1.1 (A), JP1.2, OSC1.7 (GND), P1.34, P2.1, P2.3, P2.5, P2.7, P2.9, P2.11, P2.13, P2.15, P2.17, P2.19, P2.21, P2.23, P2.25, P2.27, P2.29, P2.31, P2.33, P3.2 (PM), P4.1, SW1.1, SW1.3, U1.1 (G1), U1.10 (GND), U1.19 (G2), U2.1 (G1), U2.10 (GND), U2.19 (G2), U3.10 (GND), U4.8 (GND), U5.1 (G1), U5.9 (A7), U5.10 (GND), U5.19 (G2), U6.14 (GND), U7.7 (GND), U7.19 (GND), U7.32 (GND), U7.42 (GND), U7.47 (GND), U7.59 (GND), U7.72 (GND), U7.82 (GND), U8.20 (GND), U9.4 (GND), U10.7 (GND), U11.8 (GND), U11.14 (Eb1)
unnamed: C1.2, U4.6 (Cext)
unnamed: R3.1, RV1.3
unnamed: C3.2, U4.14 (Cext)
unnamed: U5.15 (Y3), U9.1 (DSKD)
unnamed: C1.1, R1.2, U4.7 (RCext)
unnamed: C2.1, R2.2, SW1.2, U5.3 (A1)
unnamed: U8.27 (RDATA), U9.7 (SEPD)
unnamed: U8.26 (RCLK), U9.2 (SEPCLK)
unnamed: U8.16 (DIR), U10.13
unnamed: U8.30 (WGATE), U10.3
unnamed: U8.31 (WDATA), U10.5
unnamed: JP1.1, R15.2, U7.55 (I/O55)
unnamed: R9.1, U8.32 (READY)
unnamed: R4.1, U8.33 (WF)
unnamed: U4.3 (Clr), U4.12 (~Q)
unnamed: C3.1, RV1.1, RV1.2, U4.15 (RCext)
VCC: C4.1, C5.1, C6.1, C7.1, C8.1, C9.1, C10.1, C11.1, C12.1, C13.1, C14.1, C15.1, C16.1, C17.1, D1.2 (K), OSC1.14 (VCC), P1.33, P3.1, P4.2 (PM), R1.1, R2.1, R3.2, R4.2, R5.1, R6.1, R7.1, R8.1, R9.2, R10.1, R11.1, R12.1, R13.1, R14.1, R15.1, U1.20 (VCC), U2.20 (VCC), U3.20 (VCC), U4.2 (B), U4.10 (B), U4.11 (Clr), U4.16 (VCC), U5.2 (A0), U5.4 (A2), U5.20 (VCC), U6.1 (VPP), U6.26 (NC), U6.27 (~PGM), U6.28 (VCC), U7.3 (VCCINT), U7.13 (VCCIO), U7.26 (VCCIO), U7.38 (VCCIO), U7.43 (VCCINT), U7.53 (VCCIO), U7.66 (VCCIO), U7.78 (VCCIO), U8.21 (VCC), U8.22 (TST), U9.8 (VCC), U10.14 (VCC), U11.1 (Ea1), U11.16 (VCC)

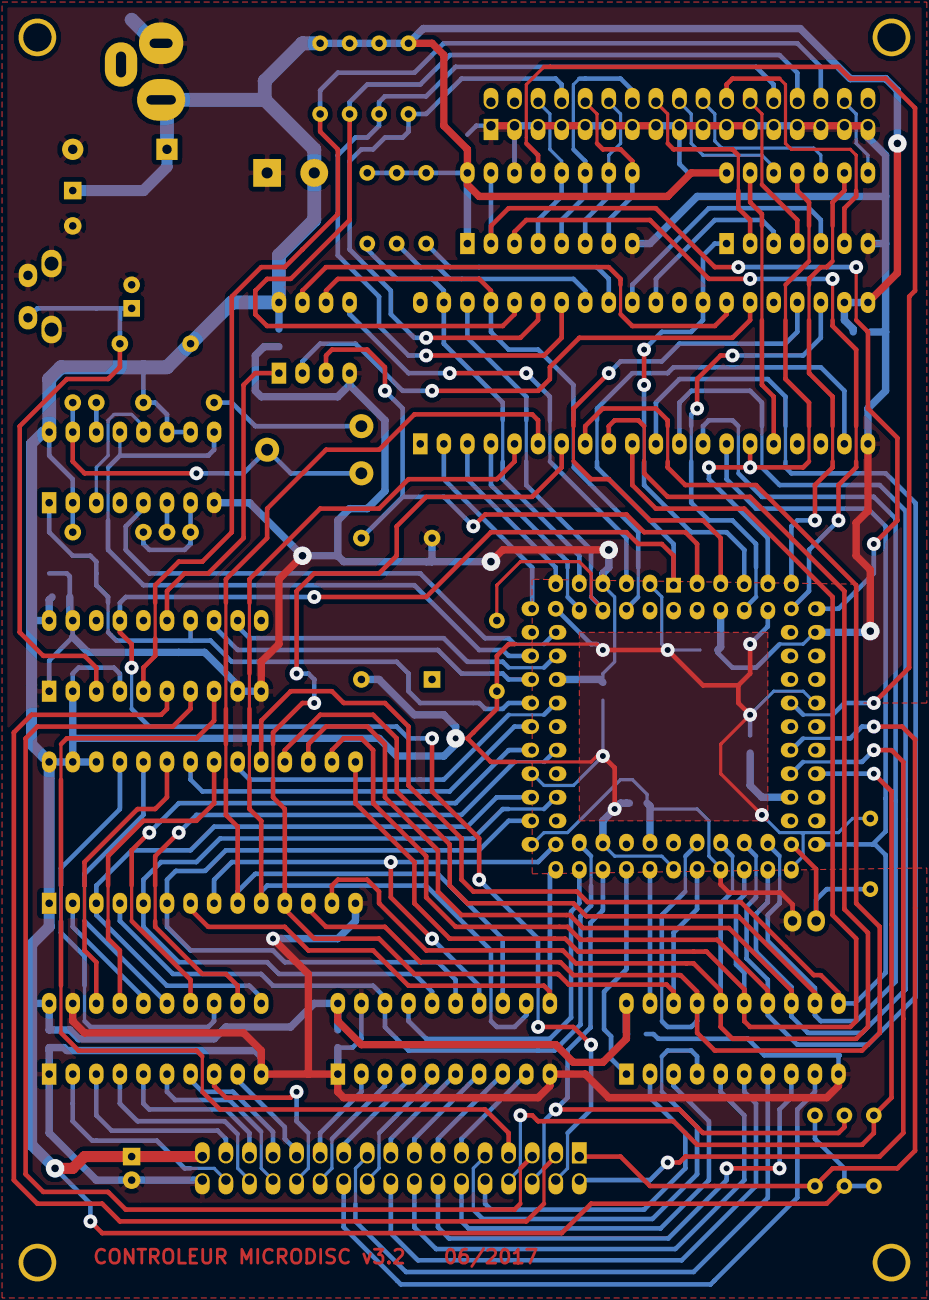
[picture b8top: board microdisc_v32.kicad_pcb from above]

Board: 2 copper layers, 56 parts (0 on the bottom side), 113 nets.

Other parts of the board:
1PIN, 1PIN#2, 1PIN#3, 1PIN#4: P***; 1pin

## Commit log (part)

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2023-05-13 Readme.md
